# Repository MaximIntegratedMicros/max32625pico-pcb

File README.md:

# max32625pico-pcb
MAX32625PICO PCB CAD Data

## Files
File Name | Description
--- | ---
max32625pico.brd  | Cadsoft Eagle Board File (7.5.0)
max32625pico.sch  | Cadsoft Eagle Schematic File (7.5.0)
output-gerb274x_4layer.cam  | Cadsoft Eagle CAM Job (7.5.0)
output/max32625pico.gpi  | Photoplotter Info File
output/max32625pico.GTL  | Top (1) copper
output/max32625pico.GTS  | Top soldermask
output/max32625pico.GTO  | Top silk screen
output/max32625pico.GTP  | Top paste
output/max32625pico.G2L  | Inner GND (2) copper
output/max32625pico.G3L  | Inner PWR (15) copper
output/max32625pico.GBL  | Bottom (16) copper
output/max32625pico.GBS  | Bottom soldermask
output/max32625pico.GBO  | Bottom silk screen
output/max32625pico.GFD  | Fab drawing
output/max32625pico.GML  | Mill Layer
output/max32625pico.dri  | Drill Station Info File
output/max32625pico.TXT  | Excellon Drill File
output/max32625pico.mnt  | Component XY Data File
output/max32625pico_sch.pdf  | PDF Schematic
output/max32625pico_fab.PDF  | PDF Fab Drawing

## Bill Of Materials
[Octopart MAX32625PICO BOM](https://octopart.com/bom-tool/UAmHV0aa)

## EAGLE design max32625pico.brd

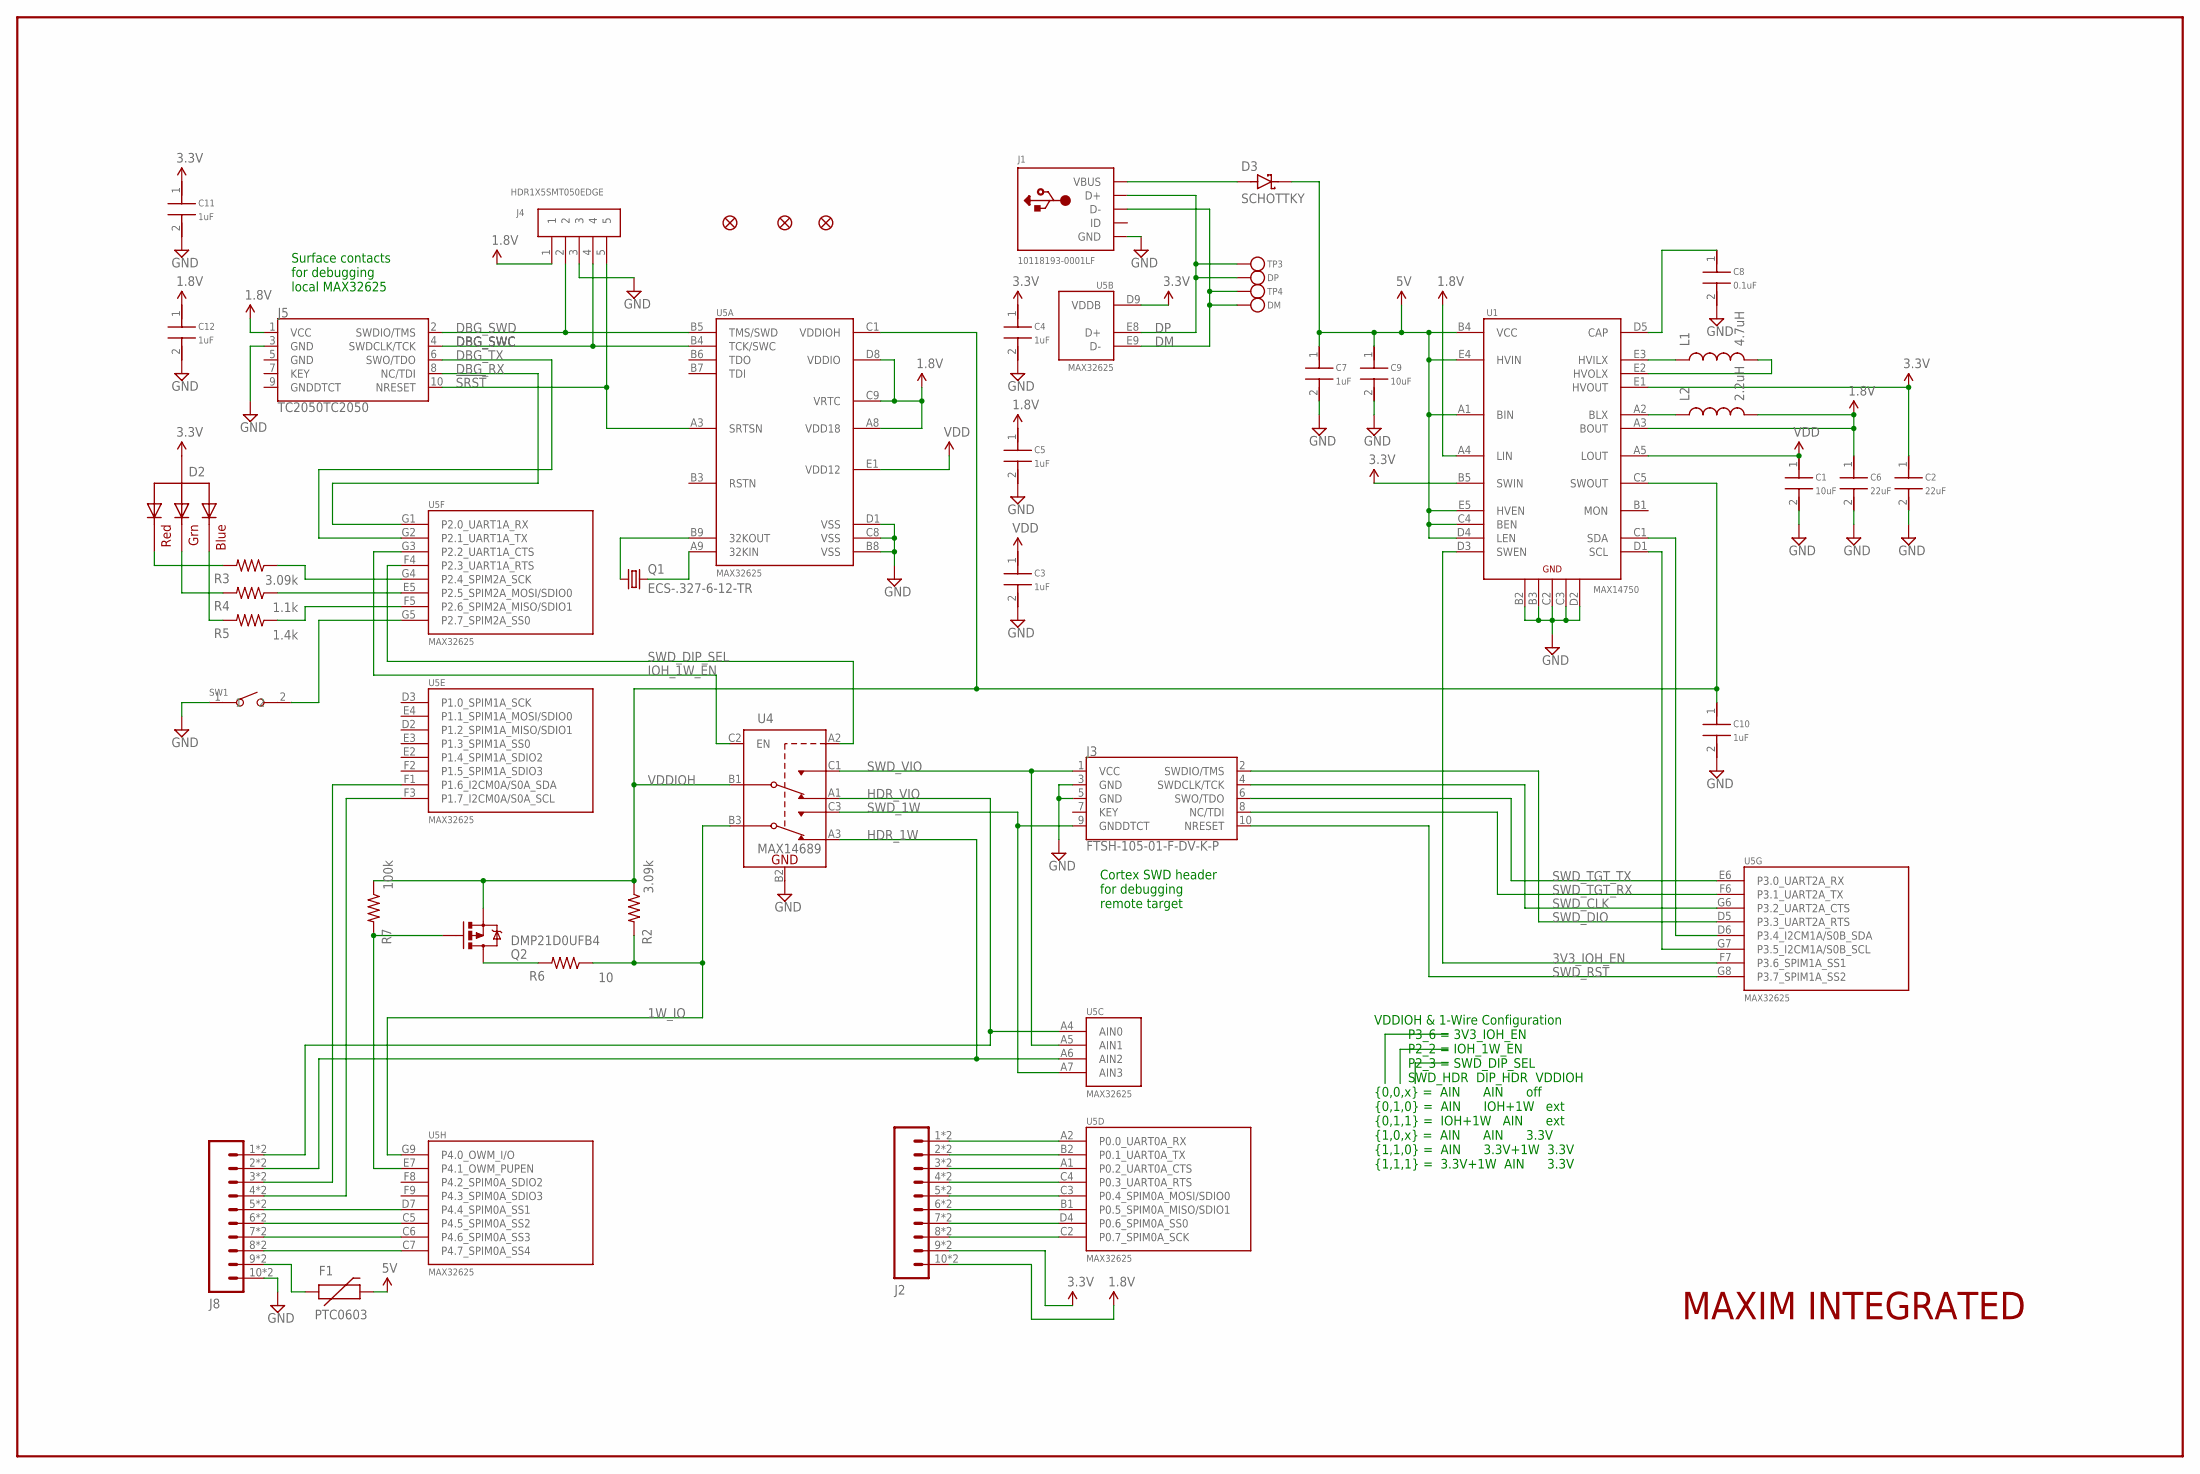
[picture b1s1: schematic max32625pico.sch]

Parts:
C1, C9: 10uF; 0402
C2, C6: 22uF; 0402
C3, C4, C5, C7, C10, C11, C12: 1uF; 0402
C8: 0.1uF; 0402
D2: RGBLED_CALUMIX-SML-LX0404; LUMIX-SML-LX0404
D3: SCHOTTKY; DCSP1006010-N1
DM: TESTPOINTROUND1.5MM; TESTPOINT_ROUND_1.5MM
DP: TESTPOINTROUND1.5MM; TESTPOINT_ROUND_1.5MM
F1: PTC0603; 0603
FD1, FD2, FD5: FIDUCIALUFIDUCIAL; MICRO-FIDUCIAL
J1: 10118193-0001LF; MICRO-USB5+6P-SMD-0.65-B
J2: M10SMT_L; 1X10_SMT_L
J3: FTSH-105-01-F-DV-K-P; SAMTECH_FTSH-105-01
J4: HDR1X5SMT050EDGE; HDR_SMT_1X5_050_EDGE
J5: TC2050TC2050; TC2050
J8: M10SMT_R; 1X10_SMT_R
L1: 4.7uH; IND2016
L2: 2.2uH; IND2016
Q1: ECS-.327-6-12-TR; FC-12M
Q2: DMP21D0UFB4; SOT-883
R2, R3: 3.09k; 0402
R4: 1.1k; 0402
R5: 1.4k; 0402
R6: 10; 0402
R7: 100k; 0402
SW1: SMD-BUTTON(2P-3.0X2.5X1.2+0.4MM)-B3U-1000P-2P-SMD; SW2-2.6-3.0X2.5X1.2+0.4MM
TP3, TP4: TESTPOINTRECT25X50MIL; TESTPOINT_RECT_25X50MIL
U1: MAX14750; W252M2-1
U4: MAX14689; W91J1-1
U5: MAX32625; W633B3-1
U$1: MAXIM_LOGO; MXM_LOGO_6MM

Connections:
1.8V: C5.1, C6.1, C12.1, J2.10, J2.S10 (10), J4.1, J5.1 (VCC), L2.2, U1.A3 (BOUT), U1.A4 (LIN), U5.A8 (VDD18), U5.C9 (VRTC), U5.D8 (VDDIO)
1W_IO: R2.2, R6.1, U4.B3 (COM2), U5.G9 (P4.0_OWM_I/O)
3.3V: C2.1, C4.1, C11.1, D2.1 (VCC), J2.9, J2.S9 (9), U1.B5 (SWIN), U1.E1 (HVOUT), U5.D9 (VDDB)
3V3_IOH_EN: U1.D3 (SWEN), U5.F7 (P3.6_SPIM1A_SS1)
5V: C7.1, C9.1, D3.1 (C), F1.2, U1.A1 (BIN), U1.B4 (VCC), U1.C4 (BEN), U1.D4 (LEN), U1.E4 (HVIN), U1.E5 (HVEN)
!SRST: J4.5, J5.10 (NRESET), U5.A3 (SRTSN)
DBG_RX: J5.8 (NC/TDI), U5.G1 (P2.0_UART1A_RX)
DBG_SWC: J4.4, J5.4 (SWDCLK/TCK), U5.B4 (TCK/SWC)
DBG_SWD: J4.2, J5.2 (SWDIO/TMS), U5.B5 (TMS/SWD)
DBG_TX: J5.6 (SWO/TDO), U5.G2 (P2.1_UART1A_TX)
DM: DM.P$1, J1.2 (D-), TP4.P$1, U5.E9 (D-)
DP: DP.P$1, J1.3 (D+), TP3.P$1, U5.E8 (D+)
GND: C1.2, C2.2, C3.2, C4.2, C5.2, C6.2, C7.2, C8.2, C9.2, C10.2, C11.2, C12.2, J1.5 (GND), J1.S1 (GND), J1.S2 (GND), J1.S3 (GND), J1.S4 (GND), J1.S5 (GND), J1.S6 (GND), J3.3 (GND), J3.5 (GND), J4.3, J5.3 (GND), J8.10, J8.S10 (10), SW1.1, U1.B2 (GND), U1.B3 (GND), U1.C2 (GND), U1.C3 (GND), U1.D2 (GND), U4.B2 (GND), U5.B8 (VSS), U5.C8 (VSS), U5.D1 (VSS)
HDR_1W: J8.2, J8.S2 (2), U4.A3 (NC2), U5.A6 (AIN2)
HDR_VIO: J8.1, J8.S1 (1), U4.A1 (NC1), U5.A4 (AIN0)
IOH_1W_EN: U4.C2 (EN), U5.G3 (P2.2_UART1A_CTS)
unnamed: J2.1, J2.S1 (1), U5.A2 (P0.0_UART0A_RX)
unnamed: J2.2, J2.S2 (2), U5.B2 (P0.1_UART0A_TX)
unnamed: C8.1, U1.D5 (CAP)
unnamed: J2.3, J2.S3 (3), U5.A1 (P0.2_UART0A_CTS)
unnamed: J2.4, J2.S4 (4), U5.C4 (P0.3_UART0A_RTS)
unnamed: R4.1, U5.E5 (P2.5_SPIM2A_MOSI/SDIO0)
unnamed: R3.1, U5.G4 (P2.4_SPIM2A_SCK)
unnamed: R5.1, U5.F5 (P2.6_SPIM2A_MISO/SDIO1)
unnamed: D2.2 (RED), R3.2
unnamed: D2.4 (GREEN), R4.2
unnamed: D2.3 (BLUE), R5.2
unnamed: D3.2 (A), J1.1 (VBUS)
unnamed: Q1.2, U5.A9 (32KIN)
unnamed: Q1.1, U5.B9 (32KOUT)
unnamed: J2.5, J2.S5 (5), U5.C3 (P0.4_SPIM0A_MOSI/SDIO0)
unnamed: J2.6, J2.S6 (6), U5.B1 (P0.5_SPIM0A_MISO/SDIO1)
unnamed: J2.7, J2.S7 (7), U5.D4 (P0.6_SPIM0A_SS0)
unnamed: J2.8, J2.S8 (8), U5.C2 (P0.7_SPIM0A_SCK)
unnamed: F1.1, J8.9, J8.S9 (9)
unnamed: Q2.3 (D), R6.2
unnamed: J8.8, J8.S8 (8), U5.C7 (P4.7_SPIM0A_SS4)
unnamed: J8.7, J8.S7 (7), U5.C6 (P4.6_SPIM0A_SS3)
unnamed: J8.6, J8.S6 (6), U5.C5 (P4.5_SPIM0A_SS2)
unnamed: J8.5, J8.S5 (5), U5.D7 (P4.4_SPIM0A_SS1)
unnamed: J8.4, J8.S4 (4), U5.F3 (P1.7_I2CM0A/S0A_SCL)
unnamed: J8.3, J8.S3 (3), U5.F1 (P1.6_I2CM0A/S0A_SDA)
unnamed: SW1.2, U5.G5 (P2.7_SPIM2A_SS0)
unnamed: L1.1, U1.E3 (HVILX)
unnamed: L2.1, U1.A2 (BLX)
unnamed: U1.D1 (SCL), U5.G7 (P3.5_I2CM1A/S0B_SCL)
unnamed: L1.2, U1.E2 (HVOLX)
unnamed: U1.C1 (SDA), U5.D6 (P3.4_I2CM1A/S0B_SDA)
unnamed: Q2.1 (G), R7.2, U5.E7 (P4.1_OWM_PUPEN)
SWD_1W: J3.9 (GNDDTCT), U4.C3 (NO2), U5.A7 (AIN3)
SWD_CLK: J3.4 (SWDCLK/TCK), U5.G6 (P3.2_UART2A_CTS)
SWD_DIO: J3.2 (SWDIO/TMS), U5.D5 (P3.3_UART2A_RTS)
SWD_DIP_SEL: U4.A2 (CB), U5.F4 (P2.3_UART1A_RTS)
SWD_RST: J3.10 (NRESET), U5.G8 (P3.7_SPIM1A_SS2)
SWD_TGT_RX: J3.8 (NC/TDI), U5.F6 (P3.1_UART2A_TX)
SWD_TGT_TX: J3.6 (SWO/TDO), U5.E6 (P3.0_UART2A_RX)
SWD_VIO: J3.1 (VCC), U4.C1 (NO1), U5.A5 (AIN1)
VDD: C1.1, C3.1, U1.A5 (LOUT), U5.E1 (VDD12)
VDDIOH: C10.1, Q2.2 (S), R2.1, R7.1, U1.C5 (SWOUT), U4.B1 (COM1), U5.C1 (VDDIOH)

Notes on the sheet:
Surface contacts for debugging local MAX32625
Cortex SWD header for debugging remote target
VDDIOH & 1-Wire Configuration P3_6 = 3V3_IOH_EN P2_2 = IOH_1W_EN P2_3 = SWD_DIP_SEL SWD_HDR DIP_HDR VDDIOH {0,0,x} = AIN AIN off {0,1,0} = AIN IOH+1W ext {0,1,1} = IOH+1W AIN ext {1,0,x} = AIN AIN 3.3V {1,1,0} = AIN 3.3V+1W 3.3V {1,1,1} = 3.3V+1W AIN 3.3V

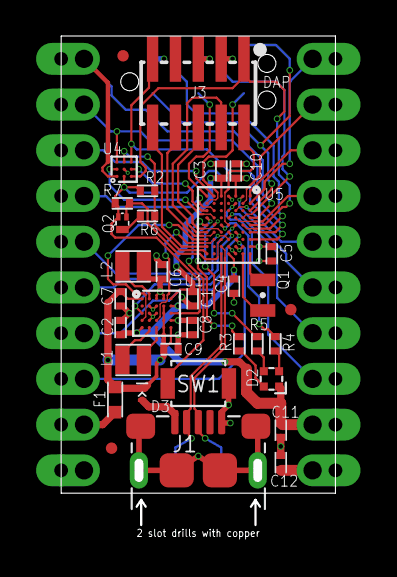
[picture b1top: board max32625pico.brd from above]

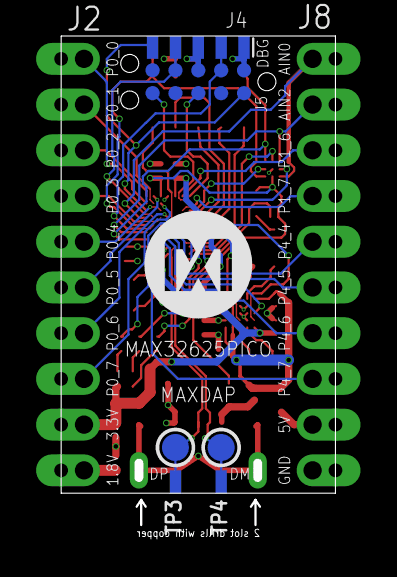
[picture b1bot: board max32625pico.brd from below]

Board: 4 copper layers, 15.2 x 27.2 mm, 44 parts (9 on the bottom side), 59 nets.

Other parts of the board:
DRILEGEND: DRILEGEND

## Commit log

2018-01-21 adding source and output files
2018-01-21 re-adding README.md for upload

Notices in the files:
parts and their libraries:
maxlib: ©2009 ROFA.cz
SparkFun-Aesthetics: Licensing: Creative Commons ShareAlike 4.0 International - https://creativecommons.org/licenses/by-sa/4.0
